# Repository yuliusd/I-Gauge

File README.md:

# I-Gauge
Open Source Hardware for monitoring water pipe pressure

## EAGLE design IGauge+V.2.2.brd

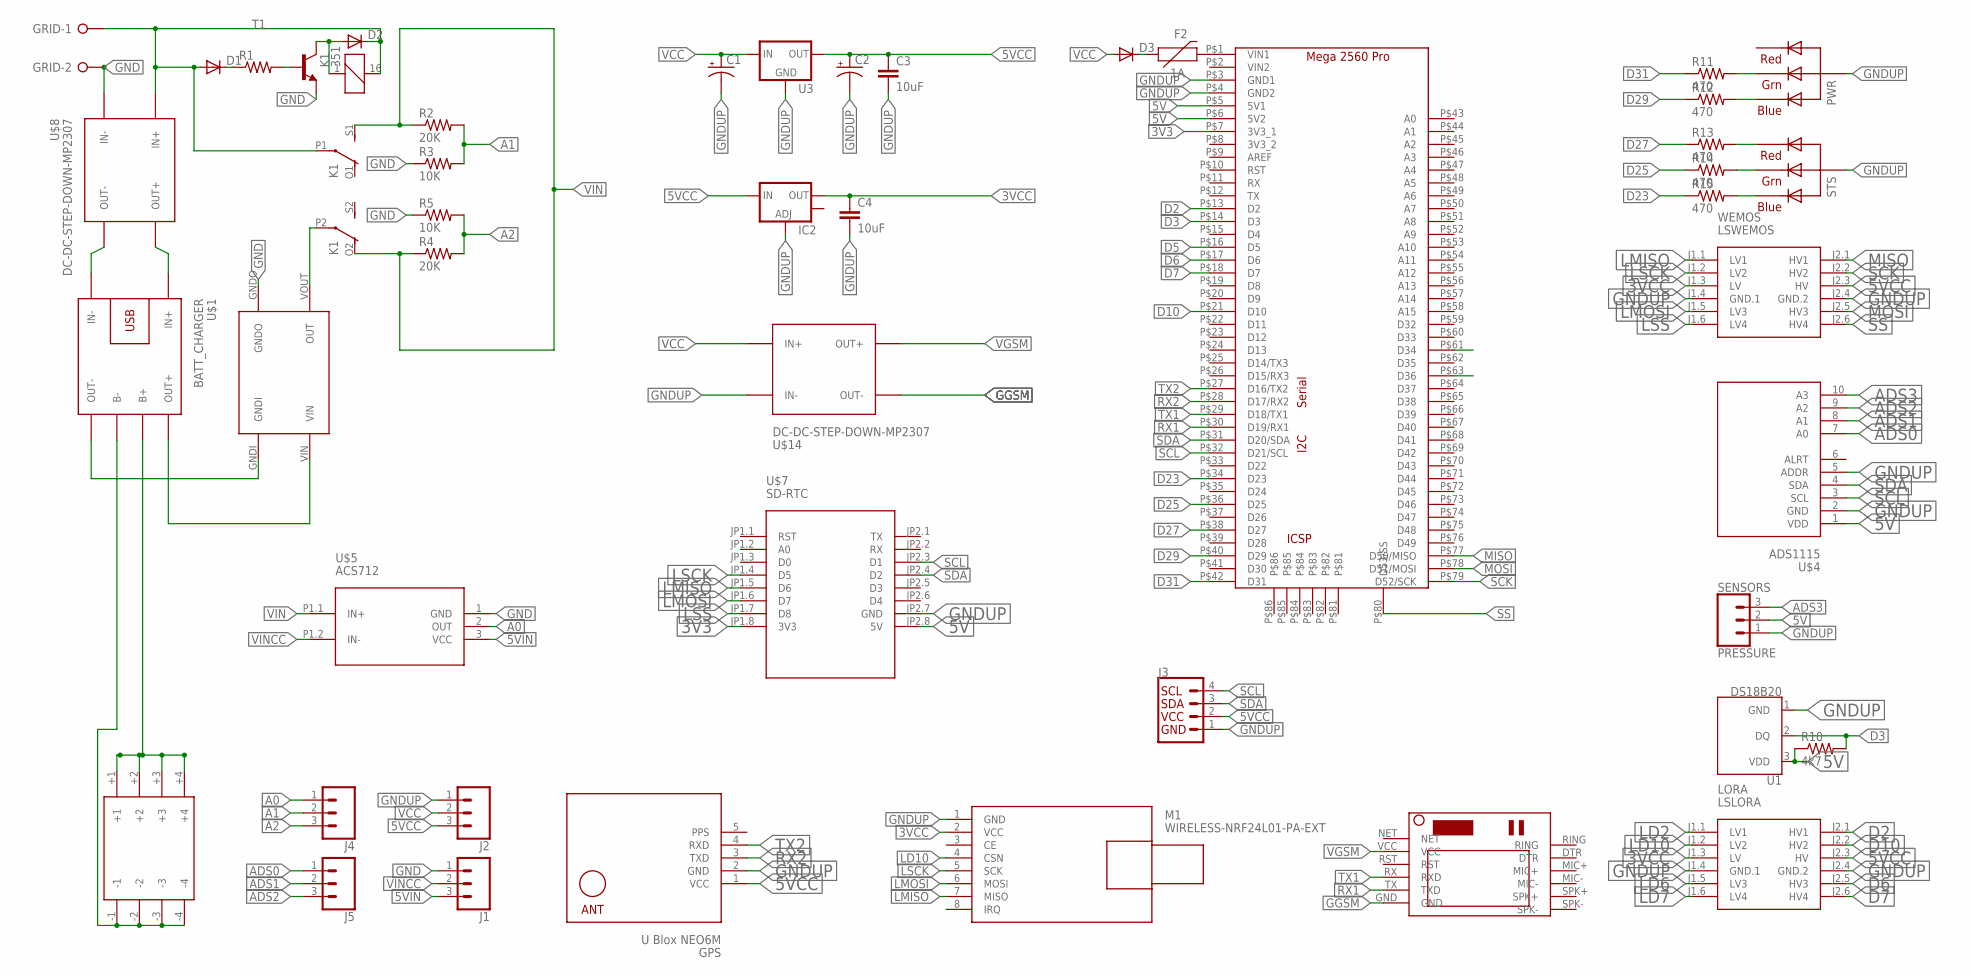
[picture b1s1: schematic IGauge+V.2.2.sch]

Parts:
C1, C2: CPOL-USD; PANASONIC_D
C3, C4: 10uF; 1206
D1, D2, D3: DIODE-SOD106A-R; SOD106A-R
F2: 1A; 1206
GPS: U Blox NEO6M; GPS-RECEIVER-NEO6M
GRID: W237-02P; W237-132
IC2: V_REG_LM1117SOT223; SOT223
J1, J2, J4, J5: CONN_03; 1X03
J3: I2C_STANDARD; 1X04
K1: 351
LORA: LSLORA; LEVEL-SHIFTER-4CH
M1: WIRELESS-NRF24L01-PA-EXT
PWR: RGBLED_CA-5MM; LED5MMRGB
R1: R-US_R1206; R1206
R2, R4: 20K; R1206
R3, R5: 10K; R1206
R10: 4k7; M1406
R11, R12, R13, R14, R15: 470; R1206
SENSORS: PRESSURE; MOLEX-1X3
STS: RGBLED_CA-5MM; LED5MMRGB
T1: -NPN-SOT23-EBC; SOT23-EBC
U1: DS18B20; TO-92-AMMO
U3: V_REG_78XX-TO-220; TO-220-ALT
U$1: BATT_CHARGER; BATTERY-CHARGER-LI-PROT
U$2: MT360_STEPUP
U$3: MEGAPROMINI
U$4: ADS1115; ADC-4CH-ADS1115
U$5: ACS712; CURRENT-SENSOR-ACS712#IC
U$7: SD-RTC; WEMOS-D1-MINI-SHIELD
U$8, U$14: DC-DC-STEP-DOWN-MP2307
U$9: 18650_4PCS_BATTERY_HOLDER
U$10: SIM800LMODULE
WEMOS: LSWEMOS; LEVEL-SHIFTER-4CH

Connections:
3V3: U$3.P$7 (3V3_1), U$7.JP1.8 (3V3)
3VCC: C4.1, IC2.2 (OUT), LORA.J1.3 (LV), M1.2 (VCC), WEMOS.J1.3 (LV)
5V: R10.1, SENSORS.2, U1.3 (VDD), U$3.P$5 (5V1), U$3.P$6 (5V2), U$4.1 (VDD), U$7.JP2.8 (5V)
5VCC: C2.+, C3.1, GPS.1 (VCC), IC2.3 (IN), J2.3, J3.2, LORA.J2.3 (HV), U3.OUT, WEMOS.J2.3 (HV)
5VIN: J1.3, U$5.3 (VCC)
A0: J4.1, U$5.2 (OUT)
A1: J4.2, R2.2, R3.2
A2: J4.3, R4.2, R5.2
ADS0: J5.1, U$4.7 (A0)
ADS1: J5.2, U$4.8 (A1)
ADS2: J5.3, U$4.9 (A2)
ADS3: SENSORS.3, U$4.10 (A3)
D2: LORA.J2.1 (HV1), U$3.P$13 (D2)
D3: R10.2, U1.2 (DQ), U$3.P$14 (D3)
D5: U$3.P$16 (D5)
D6: LORA.J2.5 (HV3), U$3.P$17 (D6)
D7: LORA.J2.6 (HV4), U$3.P$18 (D7)
D10: LORA.J2.2 (HV2), U$3.P$21 (D10)
D23: R15.1, U$3.P$34 (D23)
D25: R14.1, U$3.P$36 (D25)
D27: R13.1, U$3.P$38 (D27)
D29: R12.1, U$3.P$40 (D29)
D31: R11.1, U$3.P$42 (D31)
D34: U$3.P$61 (D34)
D36: U$3.P$63 (D36)
GGSM: U$10.GND, U$14.OUT-
GND: D1.A, D2.C, GRID.1, GRID.2, J1.1, K1.16 (2), K1.P1, R3.1, R5.1, T1.E, U$2.GNDO, U$5.1 (GND), U$8.IN+, U$8.IN-
GNDUP: C1.-, C2.-, C3.2, C4.2, GPS.2 (GND), IC2.1 (ADJ), J2.1, J3.1, LORA.J1.4 (GND.1), LORA.J2.4 (GND.2), M1.1 (GND), PWR.2 (VCC), SENSORS.1, STS.2 (VCC), U1.1 (GND), U3.GND, U$1.IN-, U$3.P$3 (GND1), U$3.P$4 (GND2), U$4.2 (GND), U$4.5 (ADDR), U$7.JP2.7 (GND), U$8.OUT-, U$14.IN-, WEMOS.J1.4 (GND.1), WEMOS.J2.4 (GND.2)
LD2: LORA.J1.1 (LV1)
LD6: LORA.J1.5 (LV3)
LD7: LORA.J1.6 (LV4)
LD10: LORA.J1.2 (LV2), M1.4 (CSN)
LMISO: M1.7 (MISO), U$7.JP1.5 (D6), WEMOS.J1.1 (LV1)
LMOSI: M1.6 (MOSI), U$7.JP1.6 (D7), WEMOS.J1.5 (LV3)
LSCK: M1.5 (SCK), U$7.JP1.4 (D5), WEMOS.J1.2 (LV2)
LSS: U$7.JP1.7 (D8), WEMOS.J1.6 (LV4)
MISO: U$3.P$77 (D50/MISO), WEMOS.J2.1 (HV1)
MOSI: U$3.P$78 (D51/MOSI), WEMOS.J2.5 (HV3)
unnamed: U$1.OUT-, U$2.GNDI
unnamed: D1.C, R1.1
unnamed: PWR.3 (GREEN), R11.2
unnamed: F2.2, U$3.P$1 (VIN1)
unnamed: D3.C, F2.1
unnamed: U$1.OUT+, U$2.VIN
unnamed: U$1.IN+, U$8.OUT+
unnamed: PWR.4 (BLUE), R12.2
unnamed: R13.2, STS.1 (RED)
unnamed: R1.2, T1.B
unnamed: D2.A, K1.1, T1.C
unnamed: U$1.B+, U$9.+1, U$9.+2, U$9.+3, U$9.+4
unnamed: U$1.B-, U$9.-1, U$9.-2, U$9.-3, U$9.-4
unnamed: R14.2, STS.3 (GREEN)
unnamed: R15.2, STS.4 (BLUE)
unnamed: K1.P2, U$2.VOUT (OUT)
PPS: GPS.5 (PPS)
RX1: U$3.P$30 (D19/RX1), U$10.TX (TXD)
RX2: GPS.3 (TXD), U$3.P$28 (D17/RX2)
SCK: U$3.P$79 (D52/SCK), WEMOS.J2.2 (HV2)
SCL: J3.4, U$3.P$32 (D21/SCL), U$4.3 (SCL), U$7.JP2.3 (D1)
SDA: J3.3, U$3.P$31 (D20/SDA), U$4.4 (SDA), U$7.JP2.4 (D2)
SS: U$3.P$80 (D53/SS), WEMOS.J2.6 (HV4)
TX1: U$3.P$29 (D18/TX1), U$10.RX (RXD)
TX2: GPS.4 (RXD), U$3.P$27 (D16/TX2)
VCC: C1.+, D3.A, J2.2, U3.IN, U$14.IN+
VGSM: U$10.VCC, U$14.OUT+
VIN: K1.O2 (O), K1.S1 (S), R2.1, R4.1, U$5.P1.1 (IN+)
VINCC: J1.2, U$5.P1.2 (IN-)

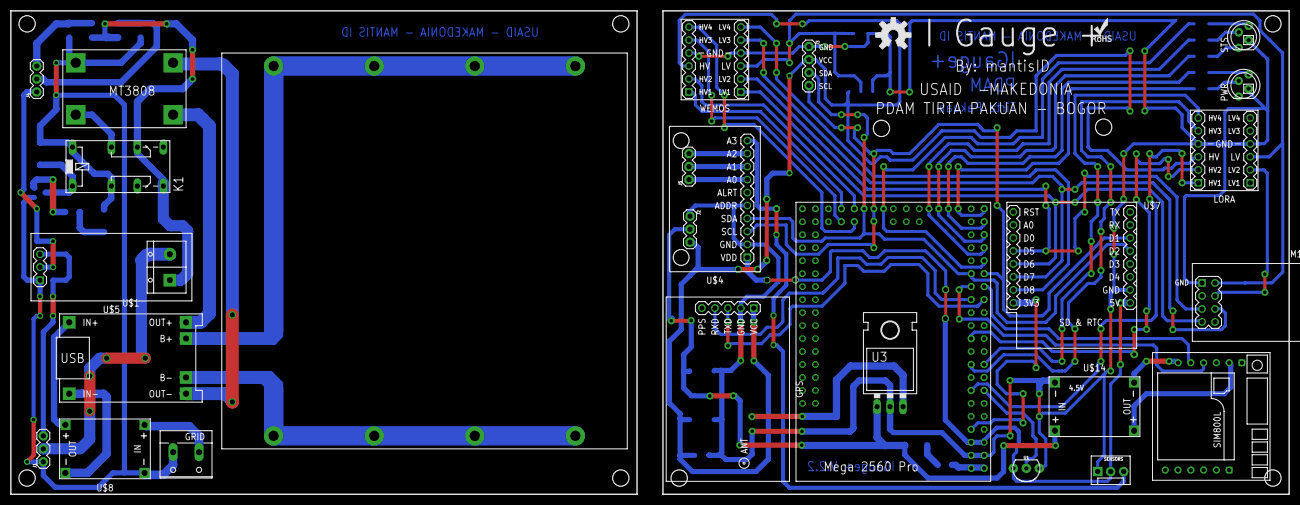
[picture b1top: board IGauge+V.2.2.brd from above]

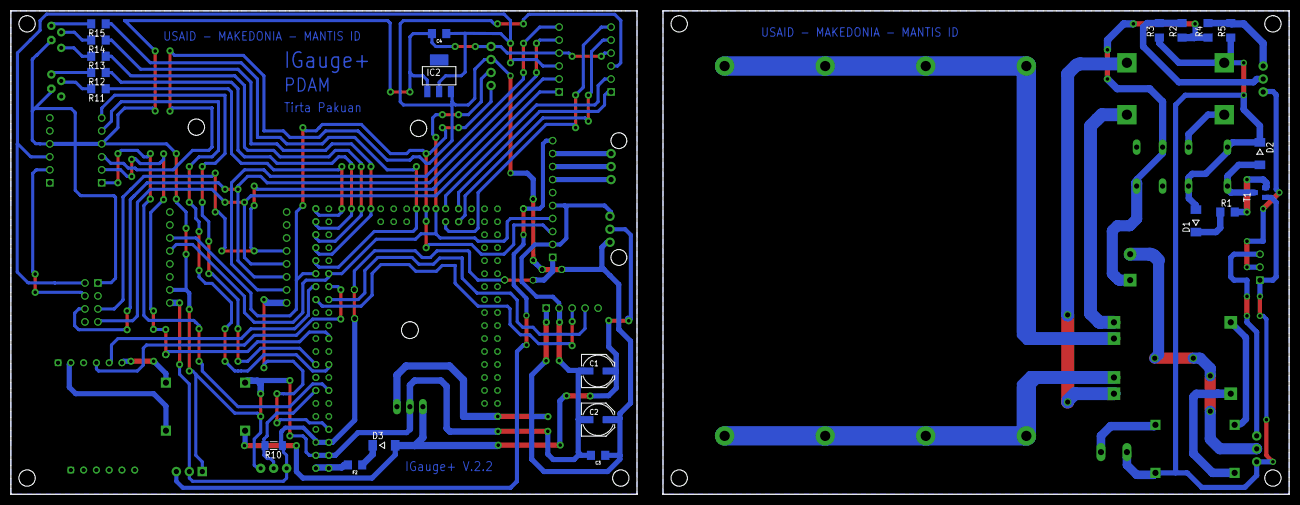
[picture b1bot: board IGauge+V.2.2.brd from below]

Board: 2 copper layers, 250.2 x 94.6 mm, 49 parts (21 on the bottom side), 60 nets.

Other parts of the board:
U$12: OSHW-LOGO-L
U$13: ROHS_LOGO_0.18_IN

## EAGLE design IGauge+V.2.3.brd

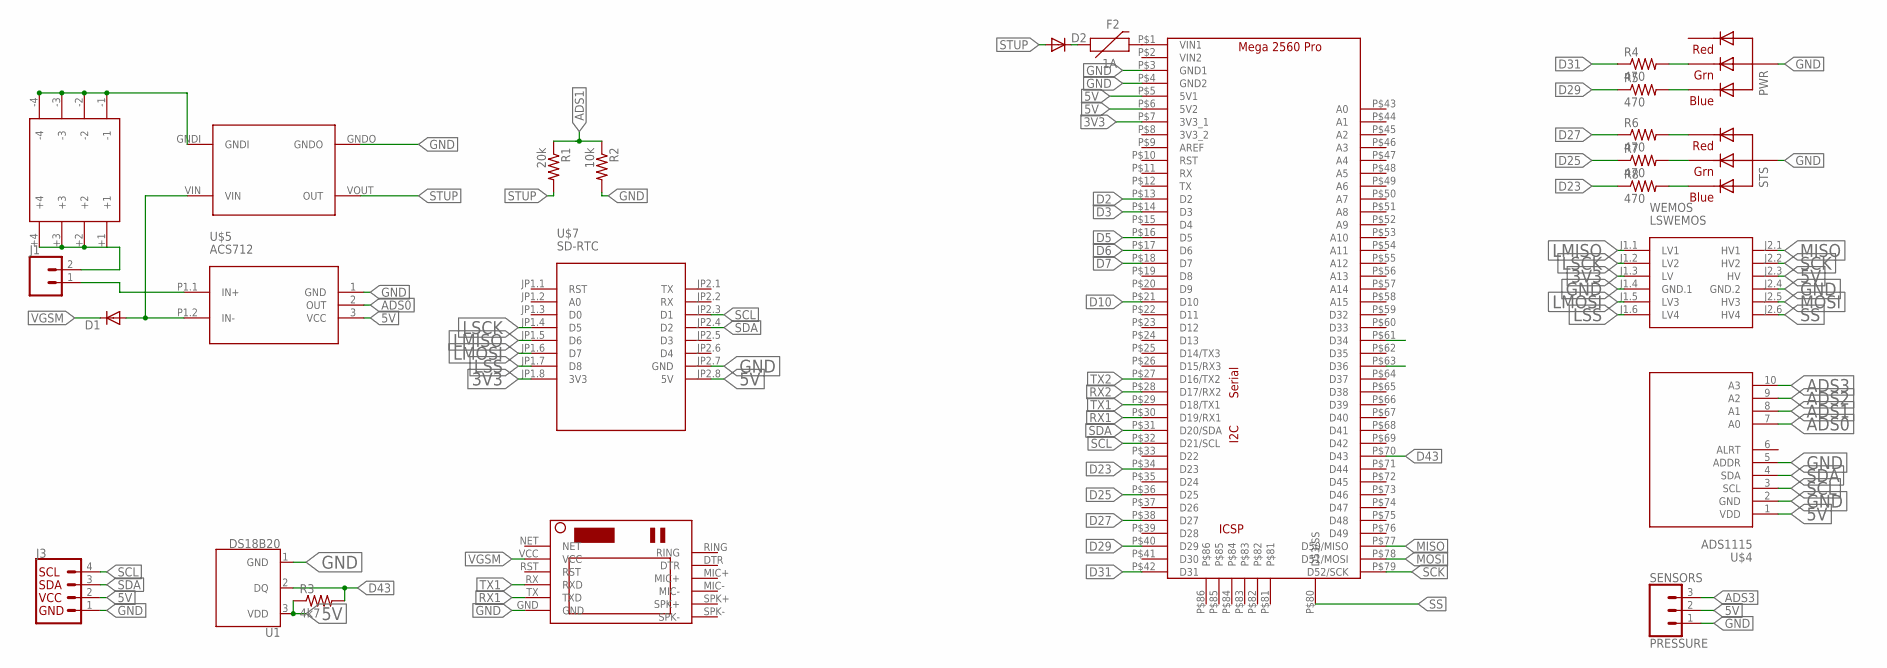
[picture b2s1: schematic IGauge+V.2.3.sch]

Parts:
D1, D2: DIODE-SOD106A-R; SOD106A-R
F2: 1A; 1206
J1: CONN_02; 1X02
J3: I2C_STANDARD; 1X04
PWR: RGBLED_CA-5MM; LED5MMRGB
R1: 20k; R1206
R2: 10k; R1206
R3: 4k7; M1406
R4, R5, R6, R7, R8: 470; R1206
SENSORS: PRESSURE; MOLEX-1X3
STS: RGBLED_CA-5MM; LED5MMRGB
U1: DS18B20; TO-92-AMMO
U$2: MT360_STEPUP
U$3: MEGAPROMINI
U$4: ADS1115; ADC-4CH-ADS1115
U$5: ACS712; CURRENT-SENSOR-ACS712#IC
U$7: SD-RTC; WEMOS-D1-MINI-SHIELD
U$9: 18650_4PCS_BATTERY_HOLDER
U$10: SIM800LMODULE
WEMOS: LSWEMOS; LEVEL-SHIFTER-4CH

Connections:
3V3: U$3.P$7 (3V3_1), U$7.JP1.8 (3V3), WEMOS.J1.3 (LV)
5V: J3.2, R3.1, SENSORS.2, U1.3 (VDD), U$3.P$5 (5V1), U$3.P$6 (5V2), U$4.1 (VDD), U$5.3 (VCC), U$7.JP2.8 (5V), WEMOS.J2.3 (HV)
ADS0: U$4.7 (A0), U$5.2 (OUT)
ADS1: R1.1, R2.1, U$4.8 (A1)
ADS2: U$4.9 (A2)
ADS3: SENSORS.3, U$4.10 (A3)
D2: U$3.P$13 (D2)
D3: U$3.P$14 (D3)
D5: U$3.P$16 (D5)
D6: U$3.P$17 (D6)
D7: U$3.P$18 (D7)
D10: U$3.P$21 (D10)
D23: R8.1, U$3.P$34 (D23)
D25: R7.1, U$3.P$36 (D25)
D27: R6.1, U$3.P$38 (D27)
D29: R5.1, U$3.P$40 (D29)
D31: R4.1, U$3.P$42 (D31)
D34: U$3.P$61 (D34)
D36: U$3.P$63 (D36)
D43: R3.2, U1.2 (DQ), U$3.P$70 (D43)
GND: J3.1, PWR.2 (VCC), R2.2, SENSORS.1, STS.2 (VCC), U1.1 (GND), U$2.GNDO, U$3.P$3 (GND1), U$3.P$4 (GND2), U$4.2 (GND), U$4.5 (ADDR), U$5.1 (GND), U$7.JP2.7 (GND), U$10.GND, WEMOS.J1.4 (GND.1), WEMOS.J2.4 (GND.2)
LMISO: U$7.JP1.5 (D6), WEMOS.J1.1 (LV1)
LMOSI: U$7.JP1.6 (D7), WEMOS.J1.5 (LV3)
LSCK: U$7.JP1.4 (D5), WEMOS.J1.2 (LV2)
LSS: U$7.JP1.7 (D8), WEMOS.J1.6 (LV4)
MISO: U$3.P$77 (D50/MISO), WEMOS.J2.1 (HV1)
MOSI: U$3.P$78 (D51/MOSI), WEMOS.J2.5 (HV3)
unnamed: J1.1, U$5.P1.1 (IN+)
unnamed: PWR.3 (GREEN), R4.2
unnamed: F2.2, U$3.P$1 (VIN1)
unnamed: D2.C, F2.1
unnamed: U$2.GNDI, U$9.-1, U$9.-4
unnamed: PWR.4 (BLUE), R5.2
unnamed: R6.2, STS.1 (RED)
unnamed: R7.2, STS.3 (GREEN)
unnamed: R8.2, STS.4 (BLUE)
RX1: U$3.P$30 (D19/RX1), U$10.TX (TXD)
RX2: U$3.P$28 (D17/RX2)
SCK: U$3.P$79 (D52/SCK), WEMOS.J2.2 (HV2)
SCL: J3.4, U$3.P$32 (D21/SCL), U$4.3 (SCL), U$7.JP2.3 (D1)
SDA: J3.3, U$3.P$31 (D20/SDA), U$4.4 (SDA), U$7.JP2.4 (D2)
SS: U$3.P$80 (D53/SS), WEMOS.J2.6 (HV4)
STUP: D2.A, R1.2, U$2.VOUT (OUT)
TX1: U$3.P$29 (D18/TX1), U$10.RX (RXD)
TX2: U$3.P$27 (D16/TX2)
VACS: D1.A, U$2.VIN, U$5.P1.2 (IN-)
VGSM: D1.C, U$10.VCC
VIN: J1.2, U$9.+1, U$9.+2, U$9.+3, U$9.+4

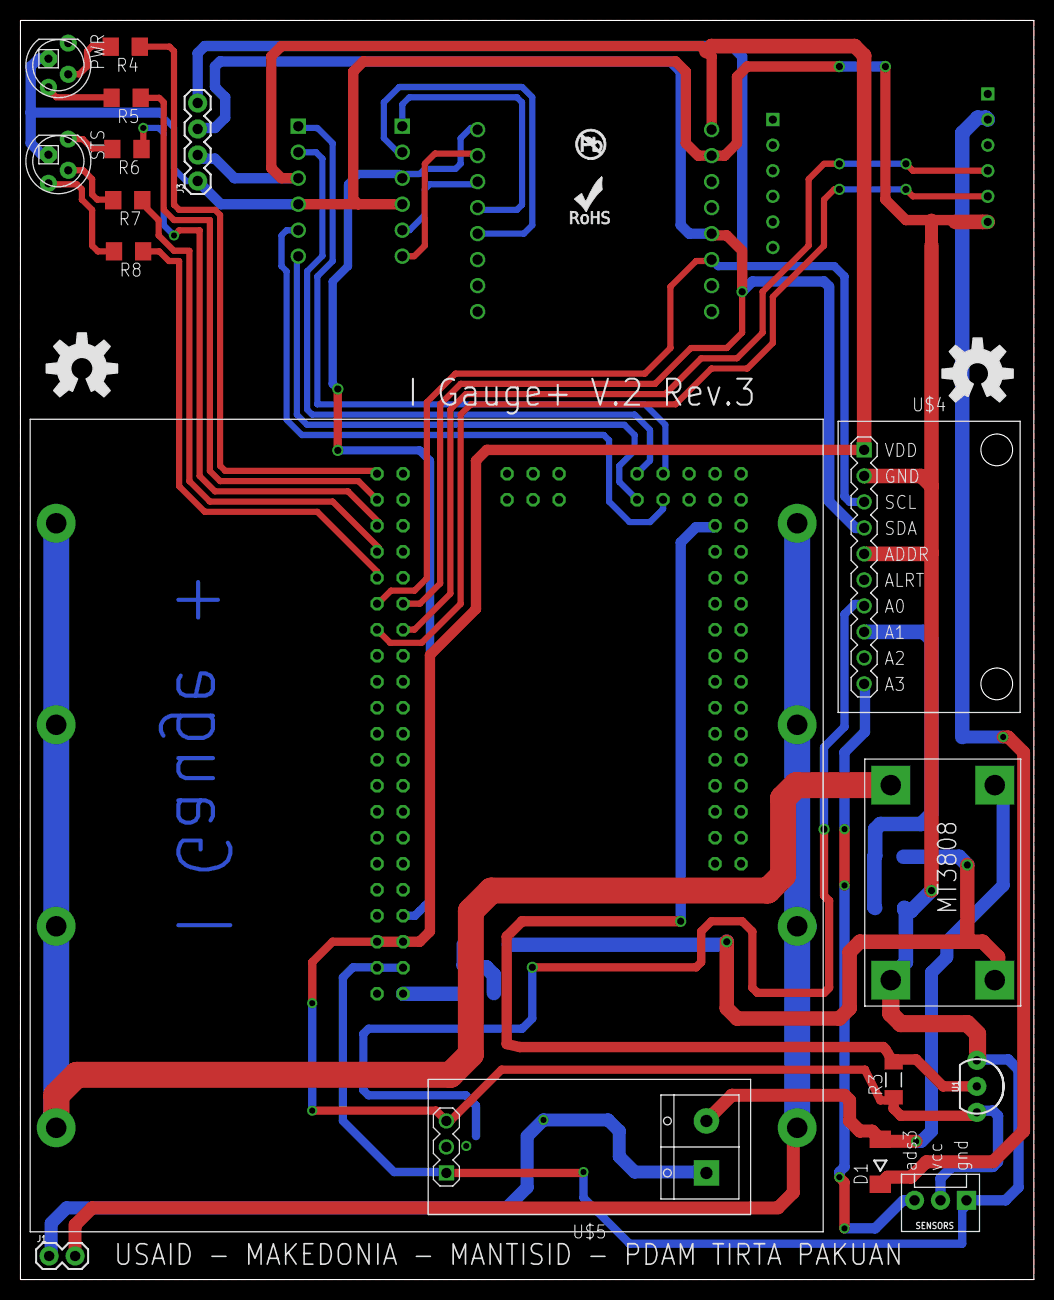
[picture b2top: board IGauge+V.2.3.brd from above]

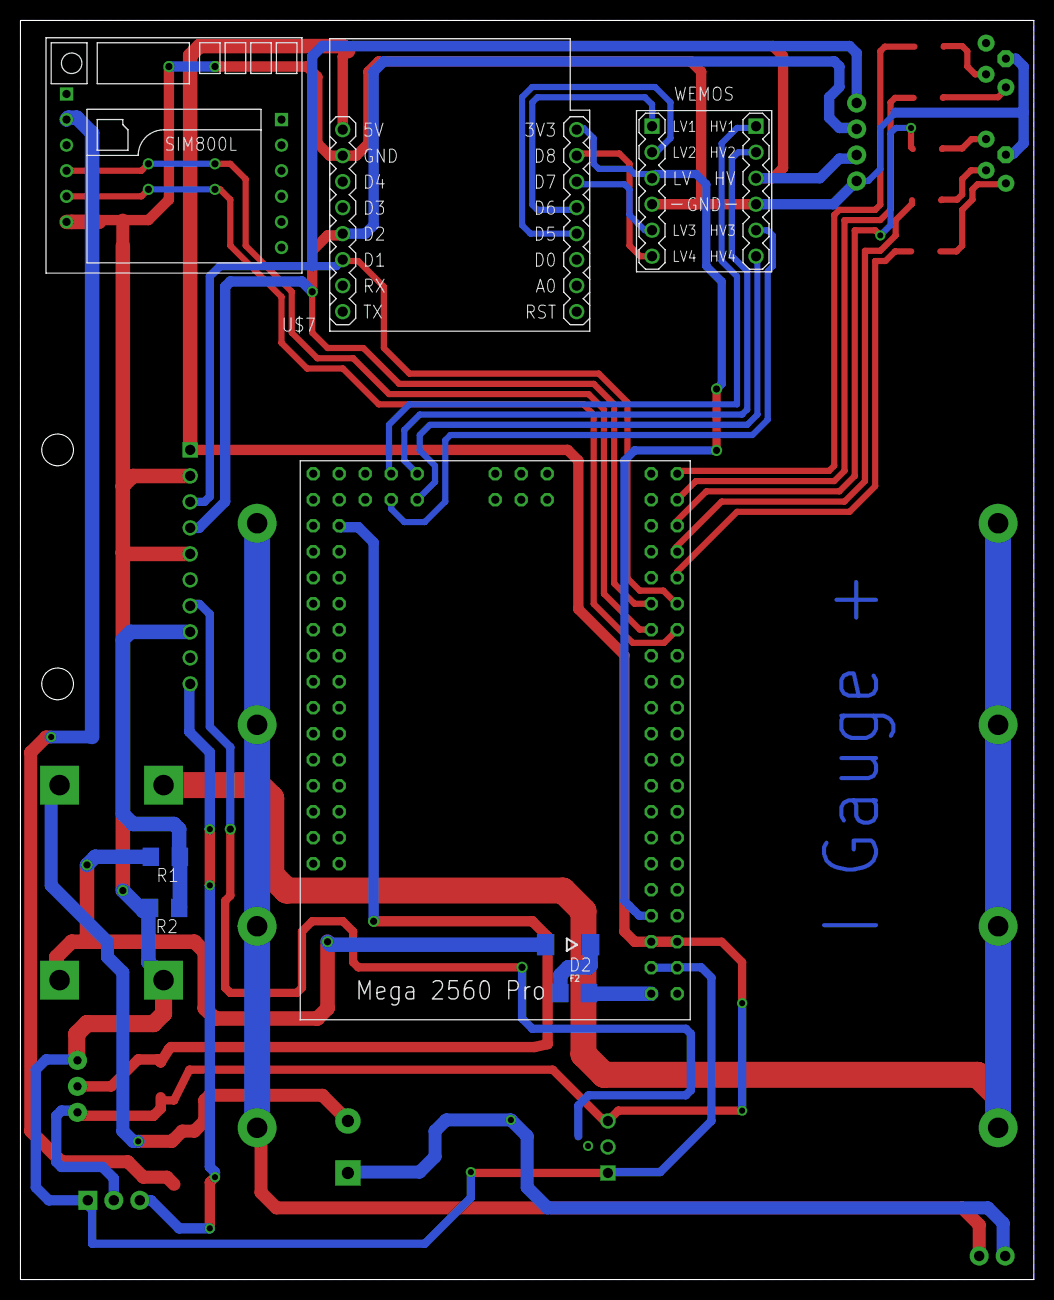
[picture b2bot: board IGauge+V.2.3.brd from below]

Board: 2 copper layers, 99.0 x 123.0 mm, 29 parts (8 on the bottom side), 37 nets.

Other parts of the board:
U$1: NO_PB_LOGO_0.120
U$6, U$8: OSHW-LOGO-L
U$11: ROHS_LOGO_0.18_IN

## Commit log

2017-10-24 Add files via upload
    gps library for proteus simulation. Based on https://www.theengineeringprojects.com/2015/12/gps-library-proteus.html
2017-10-24 Add files via upload
    Proteus simulation file
2017-11-03 Add files via upload
    Arduino sketch untuk wemos D1 esp8266.
    sketch ini digunakan untuk membuat webpage i-gauge configuration and data display
2017-12-10 Delete Arduino Mega 2560.pdsprj
    sudah tidk dibutuhkan lagi
2017-12-10 Add files via upload
    I-GAUGE Complete Version Schematic Design Using Fritzing.
    In this schematic, we use SIM800L to send data to server and LoRa to communicate with I-GAUGE LoRa Node.
2017-12-10 Update wemos.ino
    adding DNS so user can access using www.i-gauge.co.id
2017-12-10 Add files via upload
    I-GAUGE COMPLETE VERSION Fritzing file
2018-01-22 Add files via upload
    I-GAUGE V1 use 1.2 MPa pressure sensor, micro sd card, real-time clock, GPS, GSM-SIM800L, ACS712, ADS1115 and LCD 16x2.
    This version using wemos to change burst interval and data interval via the internal webpage. SIM800L used to send data to web server.
2018-01-25 Add files via upload
    Versi ini digunakan untuk I-GAUGE menggunakan baterai sebagai sumber tegangan utama. Fungsi LED di non aktifkan. Fungsi sleep ditambahkan
2018-04-26 schematic design I-GAUGE V.2.3
    final design for IGAUGE pcd development
2018-04-26 changing delay shorter

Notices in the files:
parts and their libraries:
SparkFun-Connectors: Licensing: Creative Commons ShareAlike 4.0 International - https://creativecommons.org/licenses/by-sa/4.0
diy-modules: Released under the Creative Commons Attribution 4.0 International License: http://creativecommons.org/licenses/by/4.0
